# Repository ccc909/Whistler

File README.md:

# Whistler: 16-Channel USB MEMS Microphone Array (Open Hardware)

Whistler is an open-source 16-channel circular MEMS microphone array. It plugs
into a computer over USB-C and works as a standard USB Audio Class 2 (UAC2)
microphone, with no drivers to install. An XMOS XU316 (xcore.ai) captures the
16 PDM microphones and streams them at 48 kHz. This repository has the KiCad
PCB design files, a BOM and JLCPCB production files, and the firmware.

| Mic array | Motherboard (top) | Motherboard (bottom) |
|---|---|---|
|  |  |  |

<p align="center"><em>A phone playing a 3 kHz tone is carried once around the array.<br>
Top: the phone video and the direction-of-arrival plot. Bottom: the 16 raw
channels and each mic's level at 3 kHz.</em></p>

## Key features

- **16 microphones:** Infineon IM72D128 PDM MEMS mics on a 188 mm circle with
  36.7 mm spacing. The array is designed for beamforming from about 1 kHz up to
  4.7 kHz, its spatial-aliasing limit.
- **USB audio:** an XMOS XU316 (xcore.ai) streams all 16 channels as a
  48 kHz USB Audio Class 2 microphone over USB-C.
- **Standalone:** boots from on-board QSPI flash, runs on USB bus power, and
  takes firmware updates over USB (DFU).
- **Two boards:** a 2-layer mic array and a 4-layer, 28.8 × 60.2 mm
  motherboard, linked by a 24-pin FFC.
- **Ready to order:** gerbers, a BOM with LCSC numbers, and a JLCPCB
  pick-and-place file for each board.
- **Measured:** a whistle at 125 m outdoors came through at 39 dB SNR on a
  single mic and 51 dB with the 16-mic beam, a 12.7 dB array gain. See
  [docs/measurements.md](docs/measurements.md).

<p align="center"><em>Field test: a whistle blown 125 m away at dusk, with crickets and birds in
the background.<br>Left: a single mic. Right: all 16 mics beamformed toward it.</em></p>

## Microphones

The array uses 16 Infineon [IM72D128V01](https://www.infineon.com/dgdl/Infineon-IM72D128-DataSheet-v01_01-EN.pdf)
XENSIV PDM MEMS microphones, running at 1.8 V with a 3.072 MHz PDM clock (the
datasheet's high-performance mode). Key datasheet figures at that setting:

| Parameter | Value |
|---|---|
| Signal-to-noise ratio | 72 dB(A) |
| Sensitivity | −36 dBFS ±1 dB (1 kHz, 94 dB SPL) |
| Acoustic overload point | 128 dB SPL (10% THD) |
| Dynamic range | 106 dB |
| THD | 0.5% at 94 dB SPL |
| Frequency response | −3 dB at 20 Hz, +3 dB at 19 kHz |
| Directivity | Omnidirectional |
| Ingress protection | IP57 (dust and water) |
| Supply current | 980 µA per mic (typical) |
| Package | 4 × 3 × 1.2 mm LGA |

## BOM cost

The table gives the parts cost per board in USD, not counting PCBs or assembly.
Prices were taken from LCSC on 2026-10-25, with each line rounded up to LCSC's
minimum order:

| | 1 board | 10 boards | 100 boards |
|---|---|---|---|
| Mic array | $48.96 | $34.87 | $31.40 |
| Motherboard | $27.09 | $16.34 | $14.81 |
| **Both** | **$76.05** | **$51.21** | **$46.21** |

Most of the cost is the 16 microphones ($33.57 per array at 10 boards) and the
XU316 ($10.04). LCSC doesn't sell the IM72D128 directly, so the mics are priced
from JLCPCB's parts library. FB11 can be any 0402 ferrite bead of about 600 Ω at
100 MHz.

<details>
<summary>Mic array: price per part</summary>

| Part | LCSC | Qty | 1 board | 10 boards | 100 boards |
|---|---|---|---|---|---|
| IM72D128 MEMS microphone | C5119248 | 16 | $43.36 | $33.57 | $30.37 |
| 24-pin FFC connector, Hirose FH12 | C202112 | 1 | $0.52 | $0.47 | $0.42 |
| TPS7A2018 1.8 V LDO | C963430 | 1 | $1.30 | $0.26 | $0.21 |
| 74LVC125 buffer | C6057 | 1 | $0.83 | $0.17 | $0.13 |
| 1 µF capacitor, 0402 | C14445 | 19 | $0.53 | $0.10 | $0.08 |
| 10 µF capacitor, 0603 | C18800 | 1 | $0.38 | $0.08 | $0.06 |
| 4.7 µF capacitor, 0603 | C1705 | 4 | $0.64 | $0.06 | $0.05 |
| 100 nF capacitor, 0402 | C1525 | 17 | $0.36 | $0.06 | $0.05 |
| LED, 0603 | C12624 | 1 | $0.58 | $0.06 | $0.01 |
| 33 Ω resistor, 0402 | C25105 | 16 | $0.11 | $0.02 | $0.01 |
| 22 Ω resistor, 0402 | C25092 | 4 | $0.12 | $0.01 | <$0.01 |
| 470 Ω resistor, 0402 | C25117 | 1 | $0.12 | $0.01 | <$0.01 |
| Ferrite bead, 0402 | C96691 | 1 | $0.10 | $0.01 | $0.01 |
| **Total** | | | **$48.96** | **$34.87** | **$31.40** |

</details>

<details>
<summary>Motherboard: price per part</summary>

| Part | LCSC | Qty | 1 board | 10 boards | 100 boards |
|---|---|---|---|---|---|
| XU316 xcore.ai processor | C6938291 | 1 | $10.36 | $10.04 | $10.04 |
| W25Q128JW 128 Mbit QSPI flash | C2763561 | 1 | $3.40 | $2.89 | $2.28 |
| USB-C receptacle, GCT USB4105 | C3025063 | 1 | $1.47 | $1.21 | $0.91 |
| 24-pin FFC connector, Hirose FH12 | C202112 | 1 | $0.52 | $0.47 | $0.42 |
| 750 mA resettable fuse, 1206 | C371166 | 1 | $1.08 | $0.22 | $0.17 |
| 2×10 1.27 mm header, xTAG | C22438125 | 1 | $0.81 | $0.16 | $0.13 |
| 2.2 µH inductor | C337893 | 1 | $0.78 | $0.16 | $0.13 |
| 22 µF capacitor, 0603 | C109448 | 1 | $0.76 | $0.15 | $0.13 |
| AP2112K 3.3 V LDO | C23380830 | 1 | $0.56 | $0.11 | $0.09 |
| 100 nF capacitor, 0402 | C1525 | 29 | $0.36 | $0.10 | $0.08 |
| AP2112K 1.8 V LDO | C3021123 | 1 | $0.49 | $0.10 | $0.08 |
| 24 MHz crystal, 3225 | C70590 | 1 | $0.48 | $0.10 | $0.08 |
| Ferrite bead, 0603 | C85833 | 1 | $0.92 | $0.09 | $0.02 |
| 10 µF capacitor, 0603 | C96446 | 2 | $0.87 | $0.09 | $0.07 |
| TLV62569 buck converter | C141836 | 1 | $0.36 | $0.07 | $0.06 |
| TVS diode, 0402 | C558615 | 2 | $0.69 | $0.07 | $0.05 |
| 4.7 µF capacitor, 0603 | C1705 | 3 | $0.64 | $0.06 | $0.04 |
| 1 µF capacitor, 0402 | C52923 | 5 | $0.64 | $0.06 | $0.03 |
| LED, 0603 | C2289 | 1 | $0.53 | $0.05 | $0.01 |
| 18 pF capacitor, 0402 | C1549 | 2 | $0.27 | $0.03 | $0.01 |
| 5.1 kΩ resistor, 0402 | C25905 | 2 | $0.23 | $0.02 | <$0.01 |
| 49.9 kΩ resistor, 0402 | C137969 | 1 | $0.22 | $0.02 | <$0.01 |
| 100 kΩ resistor, 0402 | C25741 | 1 | $0.15 | $0.01 | <$0.01 |
| 1 MΩ resistor, 0402 | C26083 | 1 | $0.15 | $0.01 | <$0.01 |
| 680 Ω resistor, 0402 | C25130 | 1 | $0.12 | $0.01 | <$0.01 |
| 470 Ω resistor, 0402 | C25117 | 1 | $0.12 | $0.01 | <$0.01 |
| 10 kΩ resistor, 0402 | C25744 | 3 | $0.11 | $0.01 | <$0.01 |
| **Total** | | | **$27.09** | **$16.34** | **$14.81** |

</details>

## Project structure

| Folder | Contents |
|---|---|
| [`mic-array/`](mic-array), [`motherboard/`](motherboard) | KiCad 10 projects; ordering files are in each `production/` folder |
| [`lib/`](lib) | Symbols, footprints and 3D models for both boards |
| [`firmware/`](firmware) | XU316 firmware: a prebuilt image and its source |
| [`docs/`](docs) | Renders, [manufacturing notes](docs/manufacturing.md) and [measurements](docs/measurements.md) |

## Quick start

- **Edit:** open either `*.kicad_pro` in KiCad 10. All libraries are included.
- **Order:** upload a board's `production/` files to JLCPCB. Read
  [docs/manufacturing.md](docs/manufacturing.md) first.
- **Flash:** program a new motherboard once over an xTAG on J2. After that,
  updates go over USB (DFU); see [firmware/README.md](firmware/README.md).

```bash
xflash --factory firmware/bin/whistler-mic-aggregator.xe
```

## Licence

Copyright 2026 the Whistler authors.

- **Hardware:** [CERN-OHL-S v2](LICENSE).
- **Firmware:** XMOS Public Licence v1 ([`firmware/LICENSE-XMOS.rst`](firmware/LICENSE-XMOS.rst)).
- **Library parts:** keep their own licences ([`lib/README.md`](lib/README.md)).

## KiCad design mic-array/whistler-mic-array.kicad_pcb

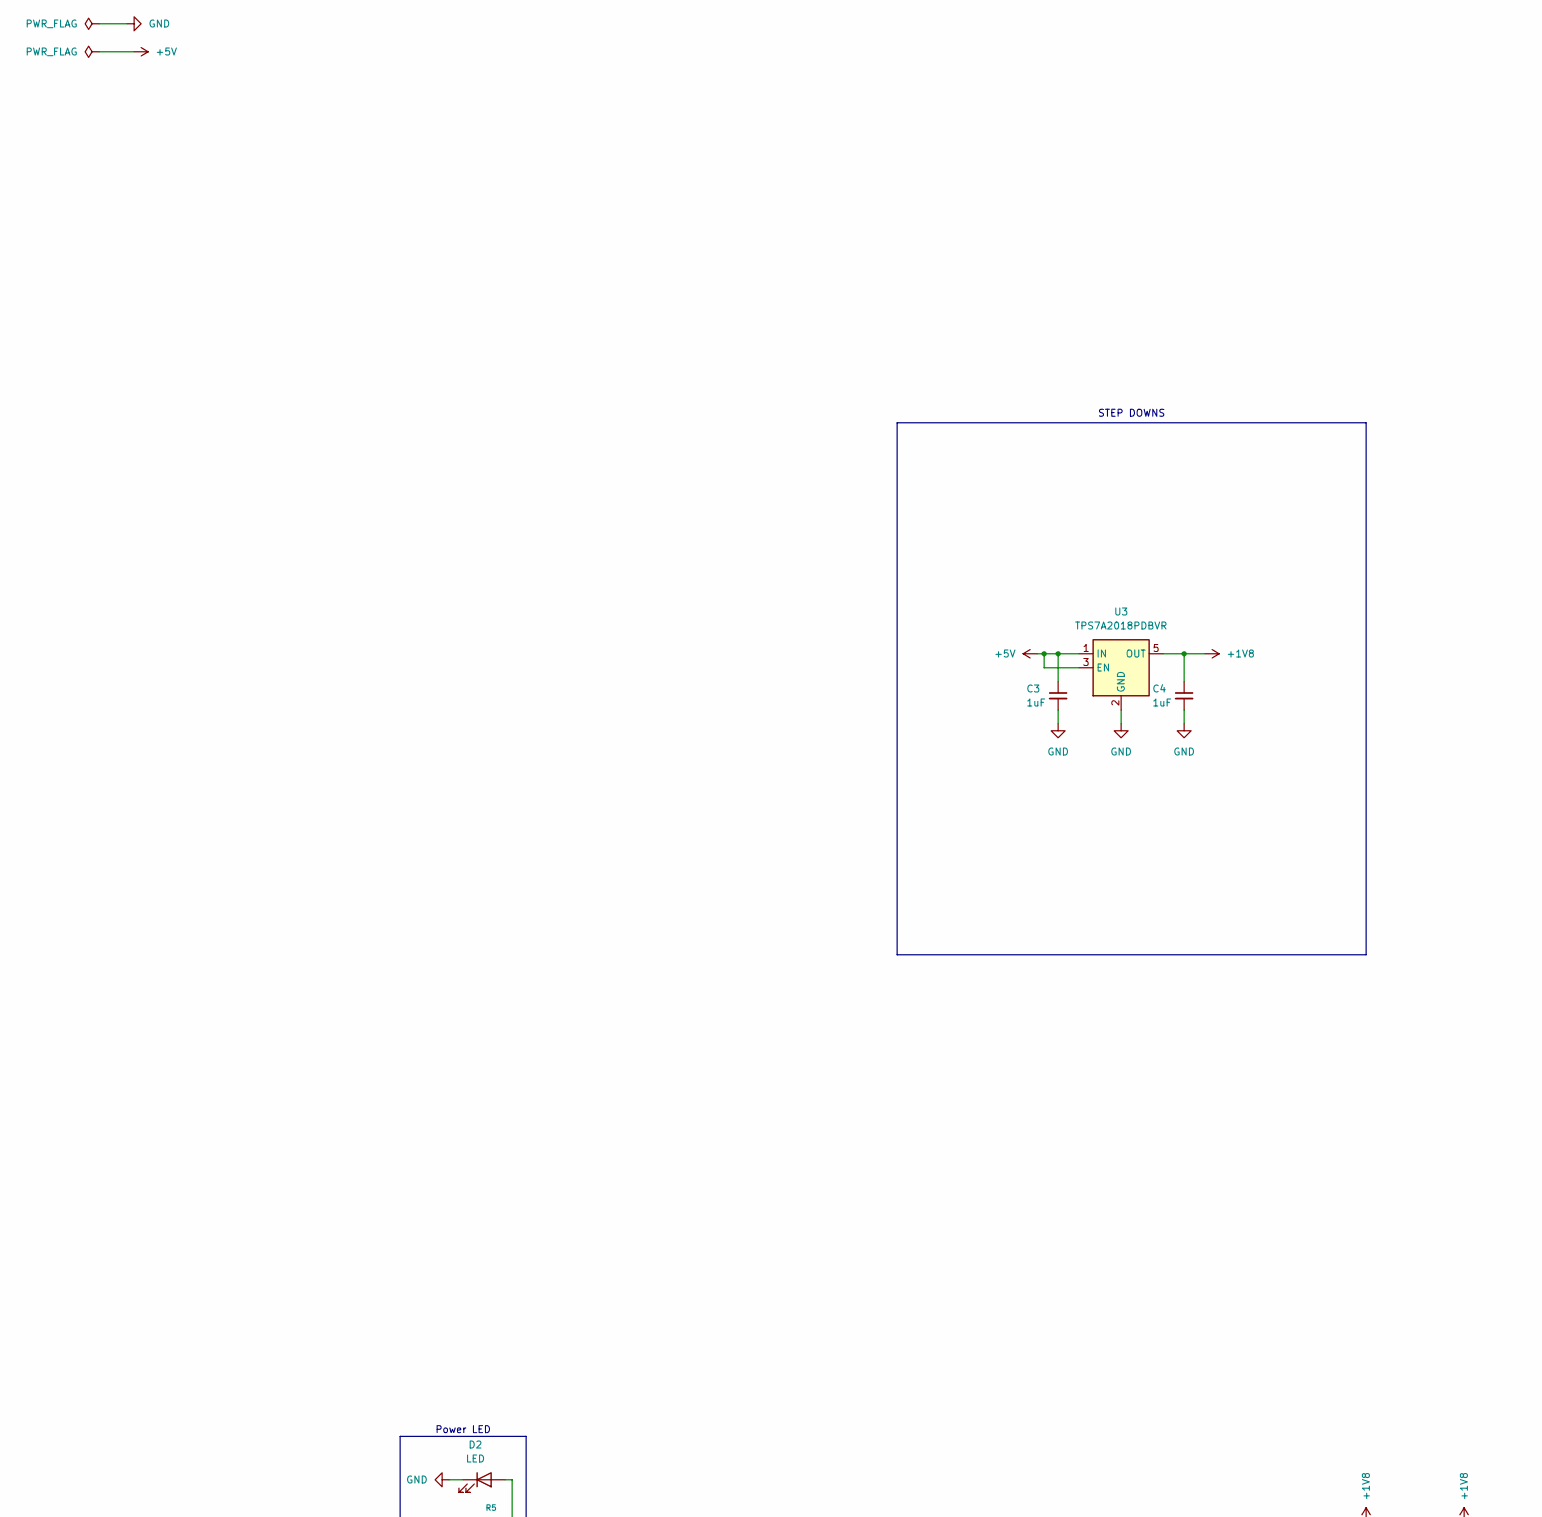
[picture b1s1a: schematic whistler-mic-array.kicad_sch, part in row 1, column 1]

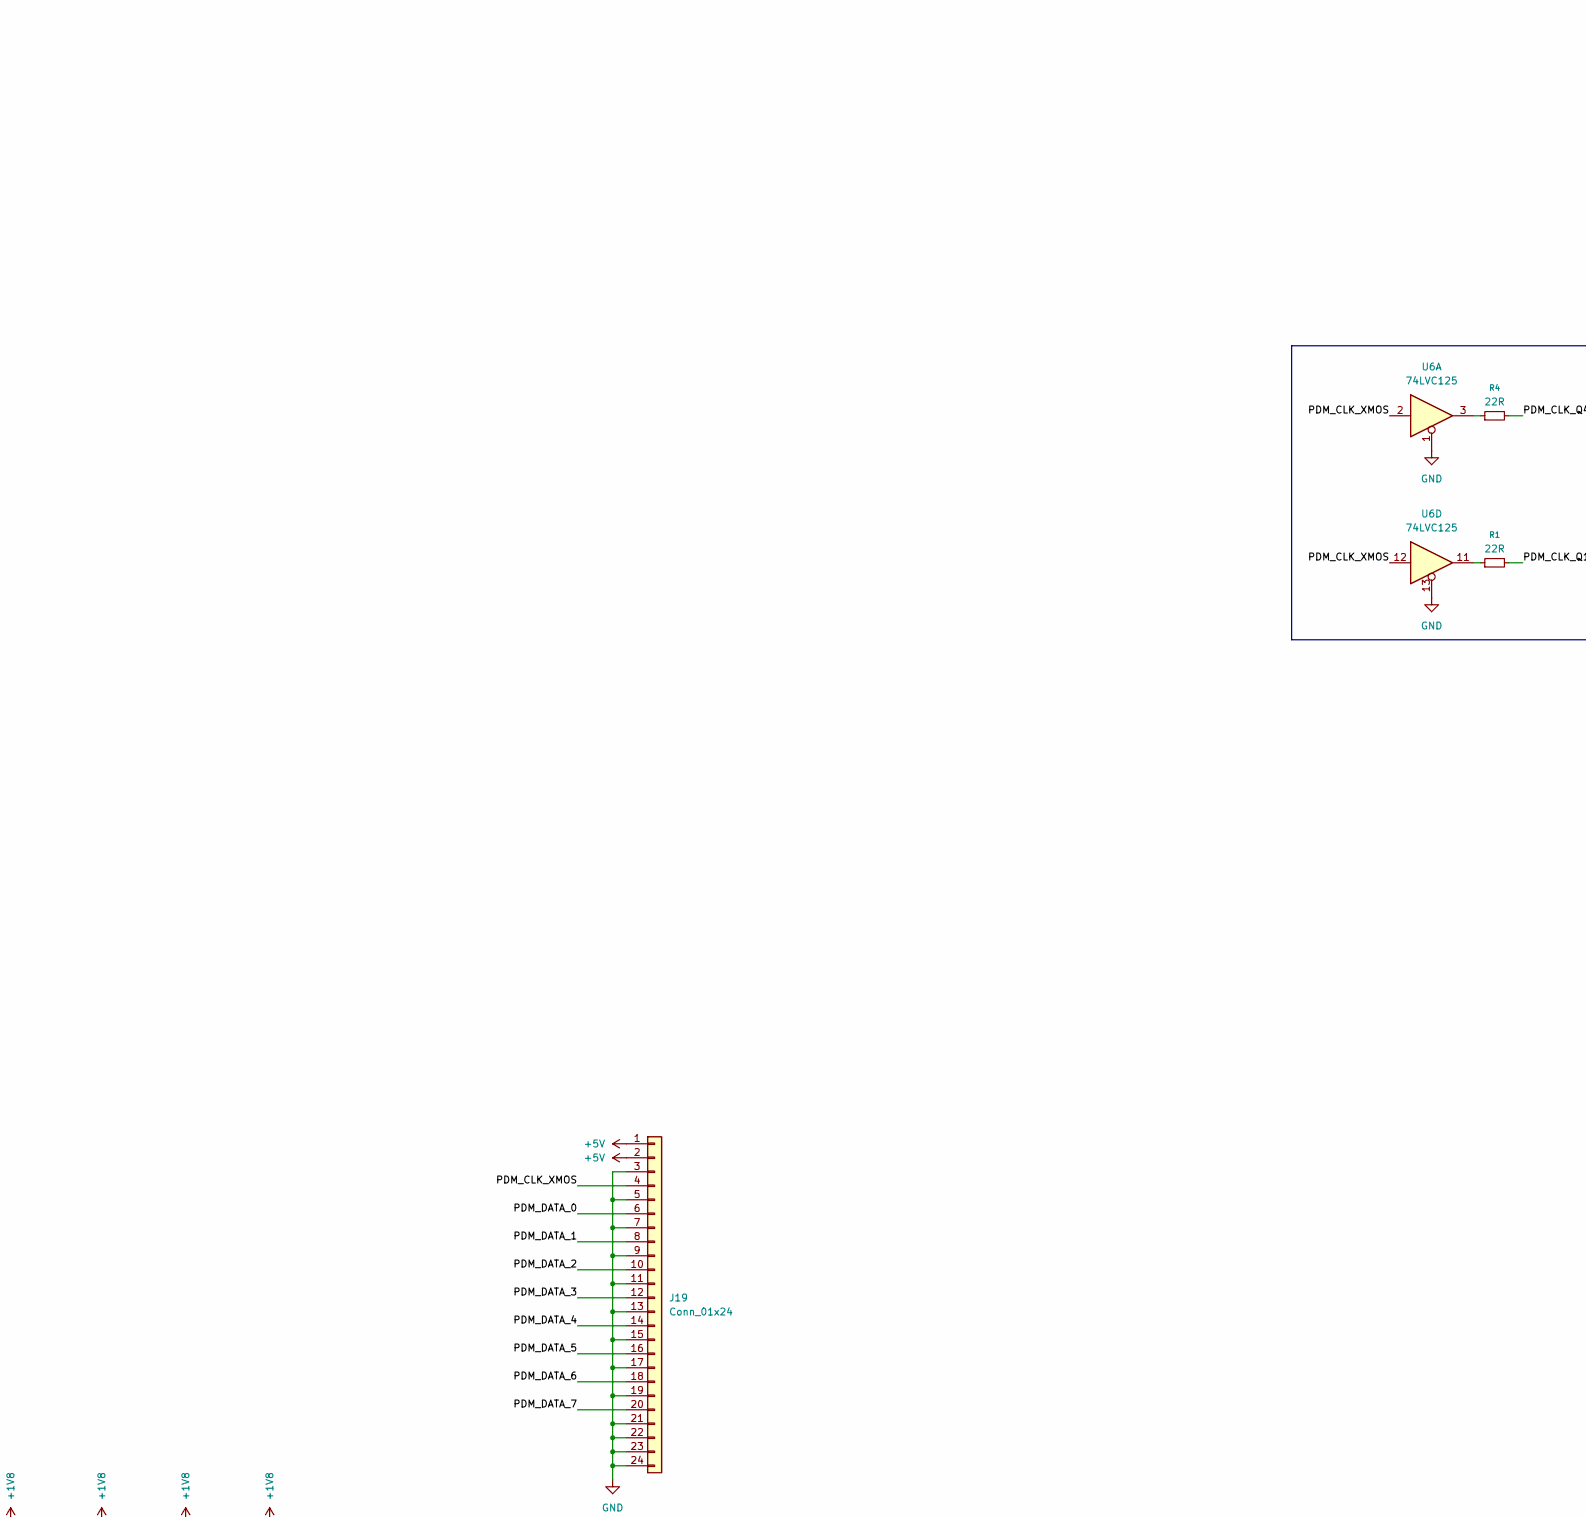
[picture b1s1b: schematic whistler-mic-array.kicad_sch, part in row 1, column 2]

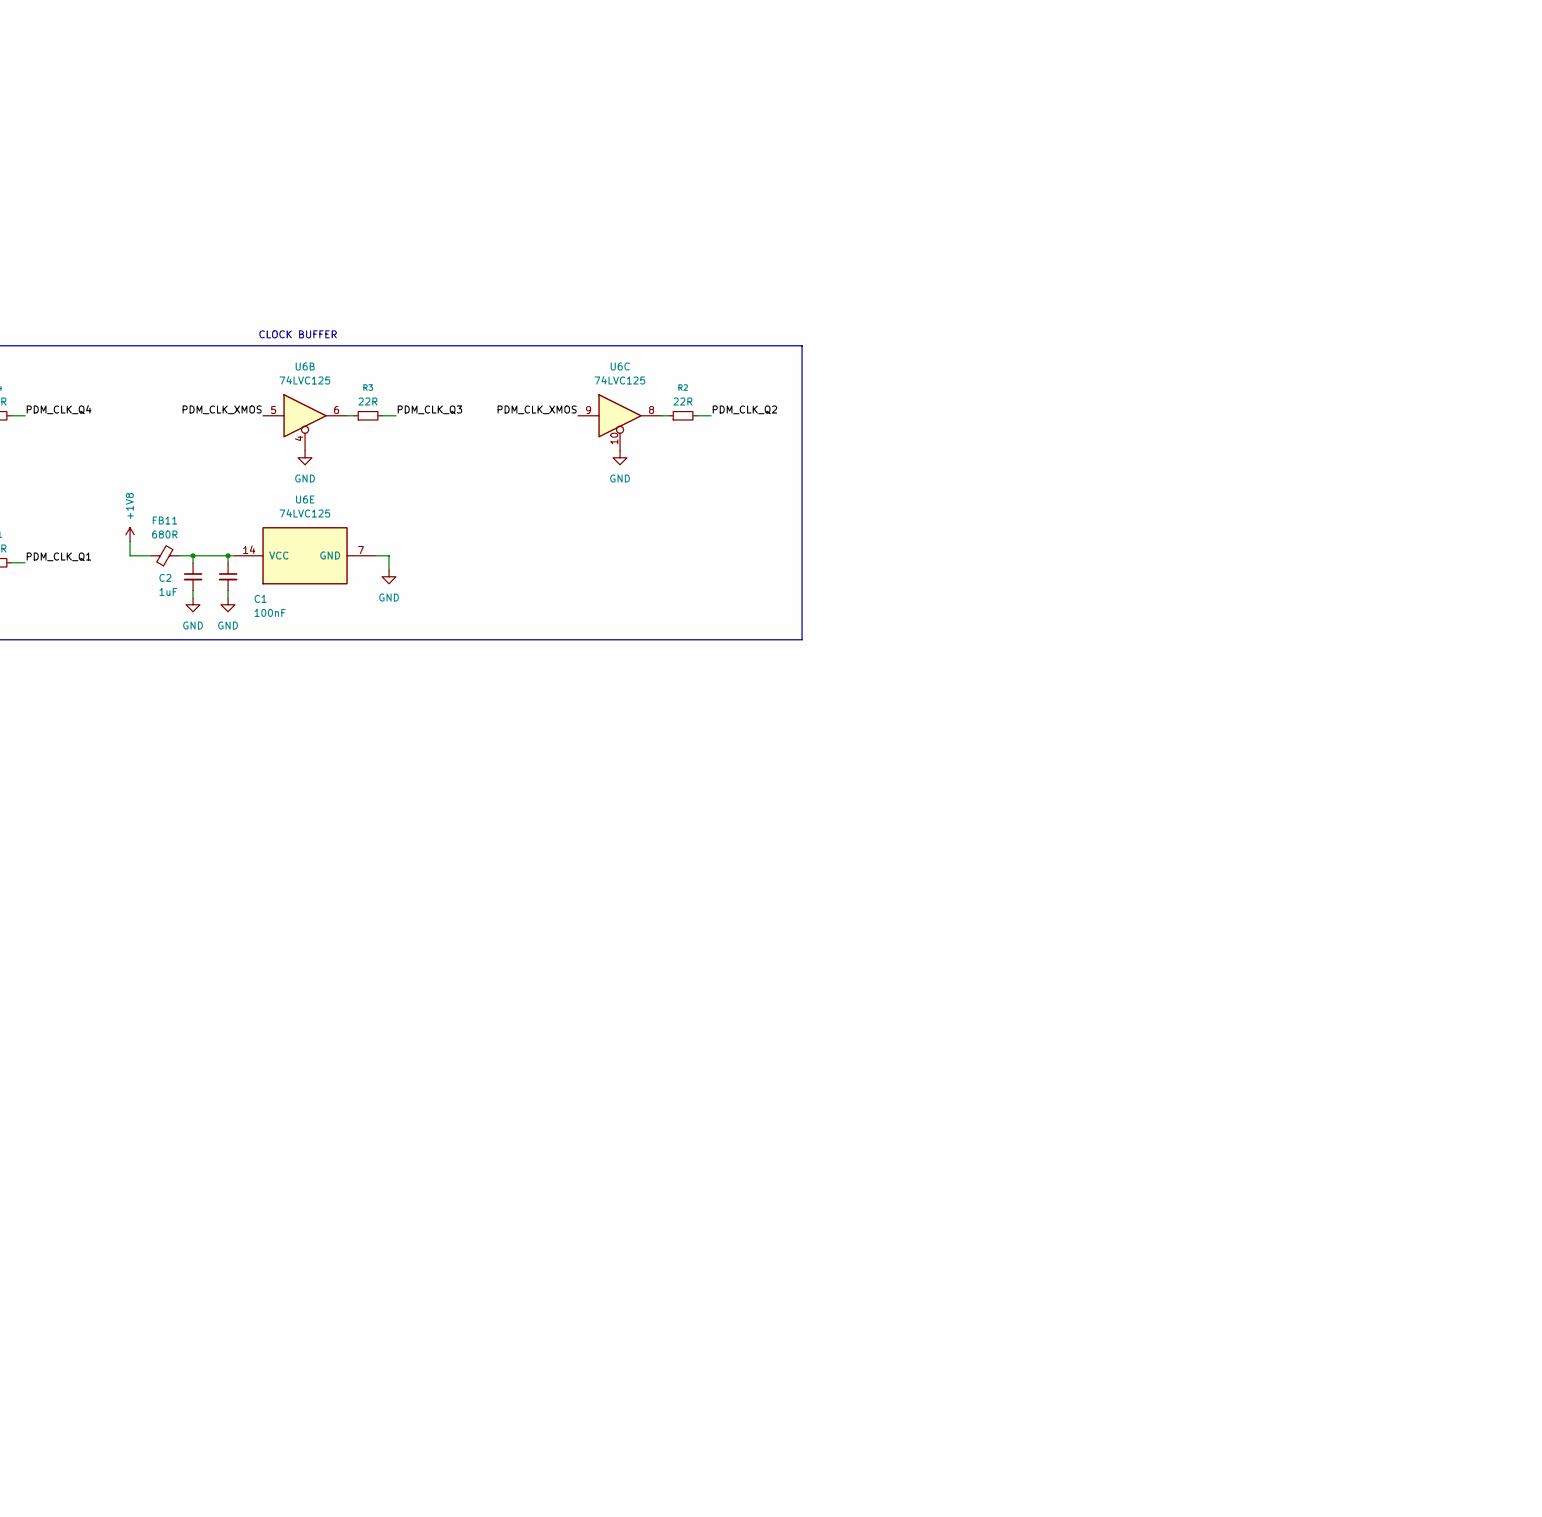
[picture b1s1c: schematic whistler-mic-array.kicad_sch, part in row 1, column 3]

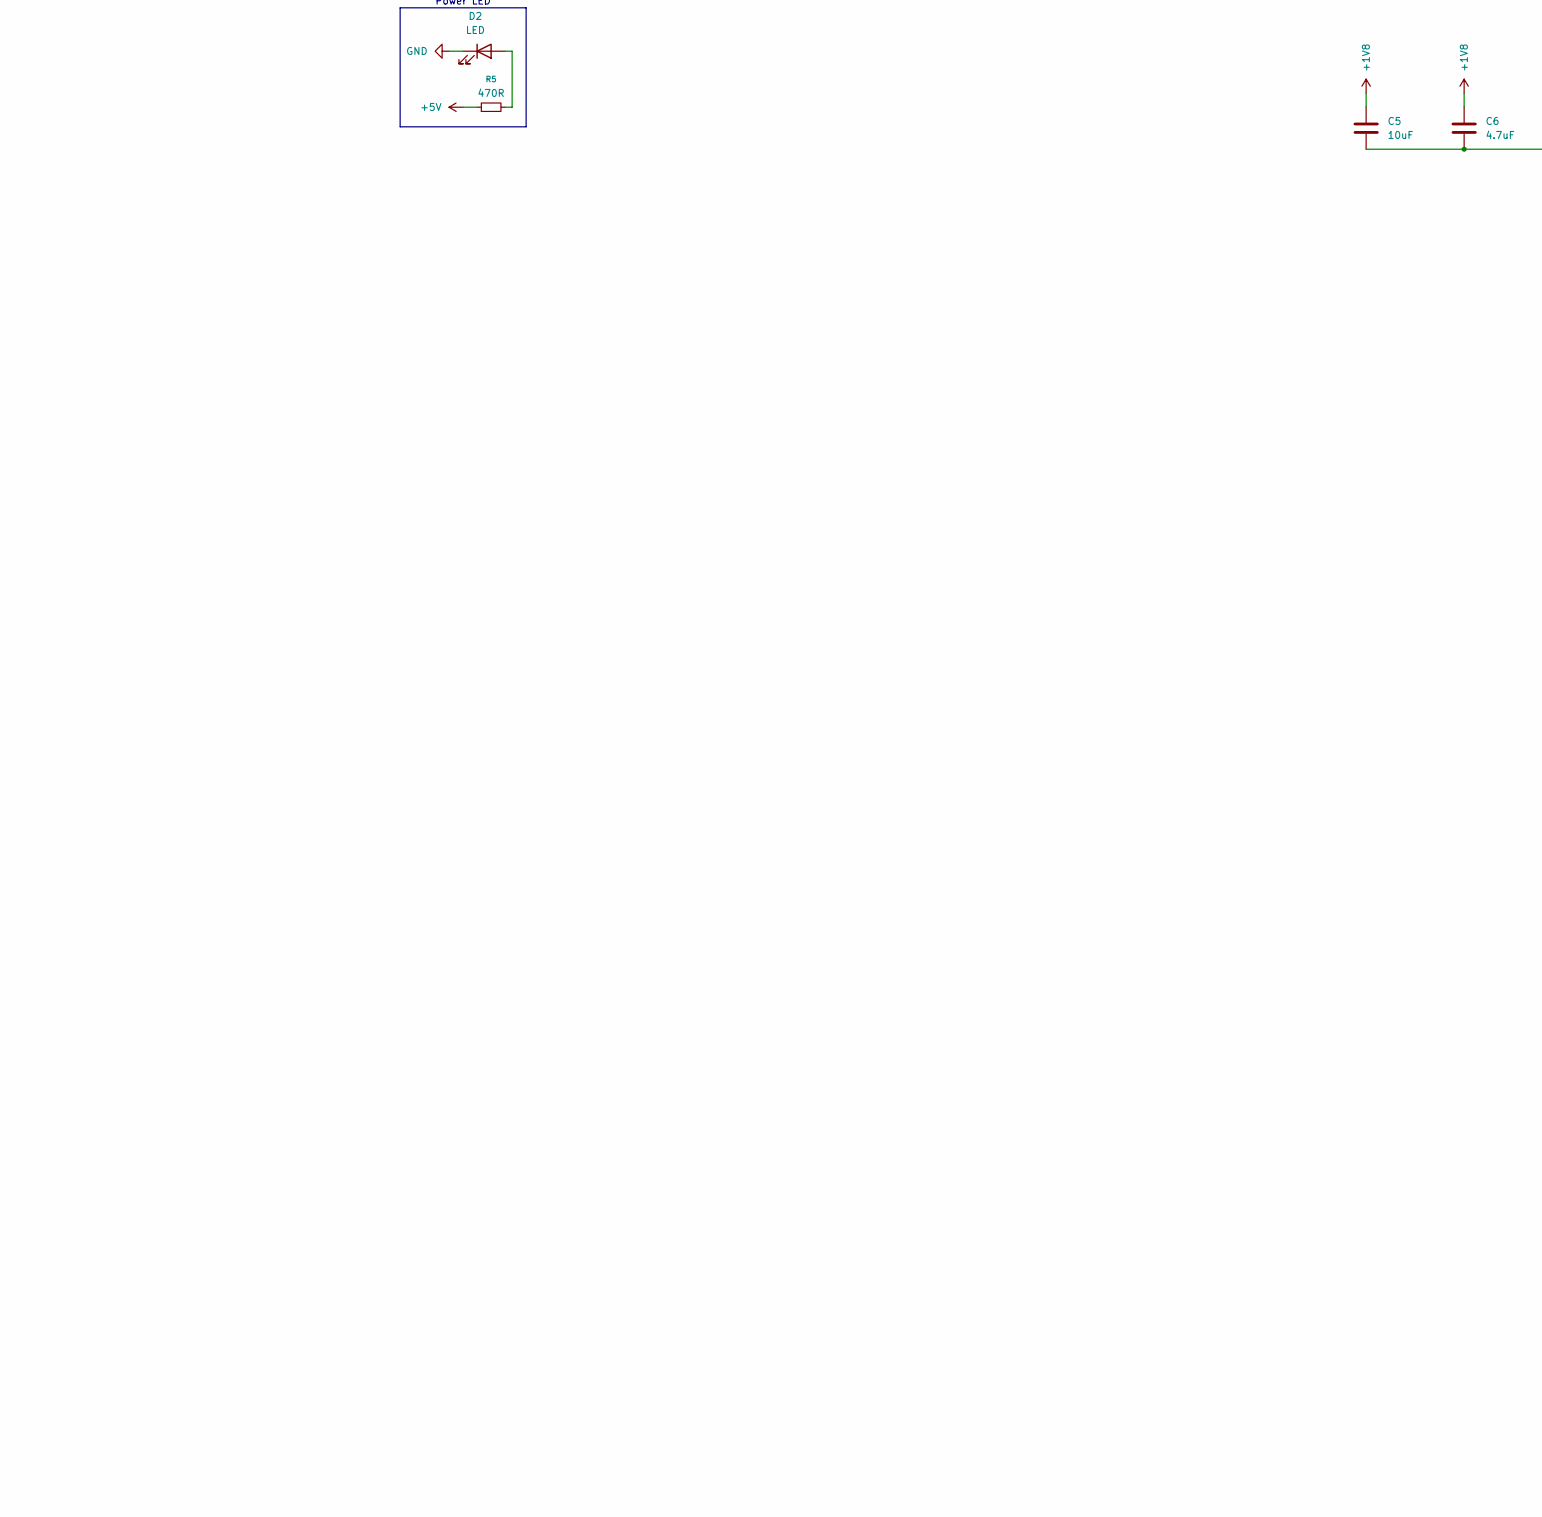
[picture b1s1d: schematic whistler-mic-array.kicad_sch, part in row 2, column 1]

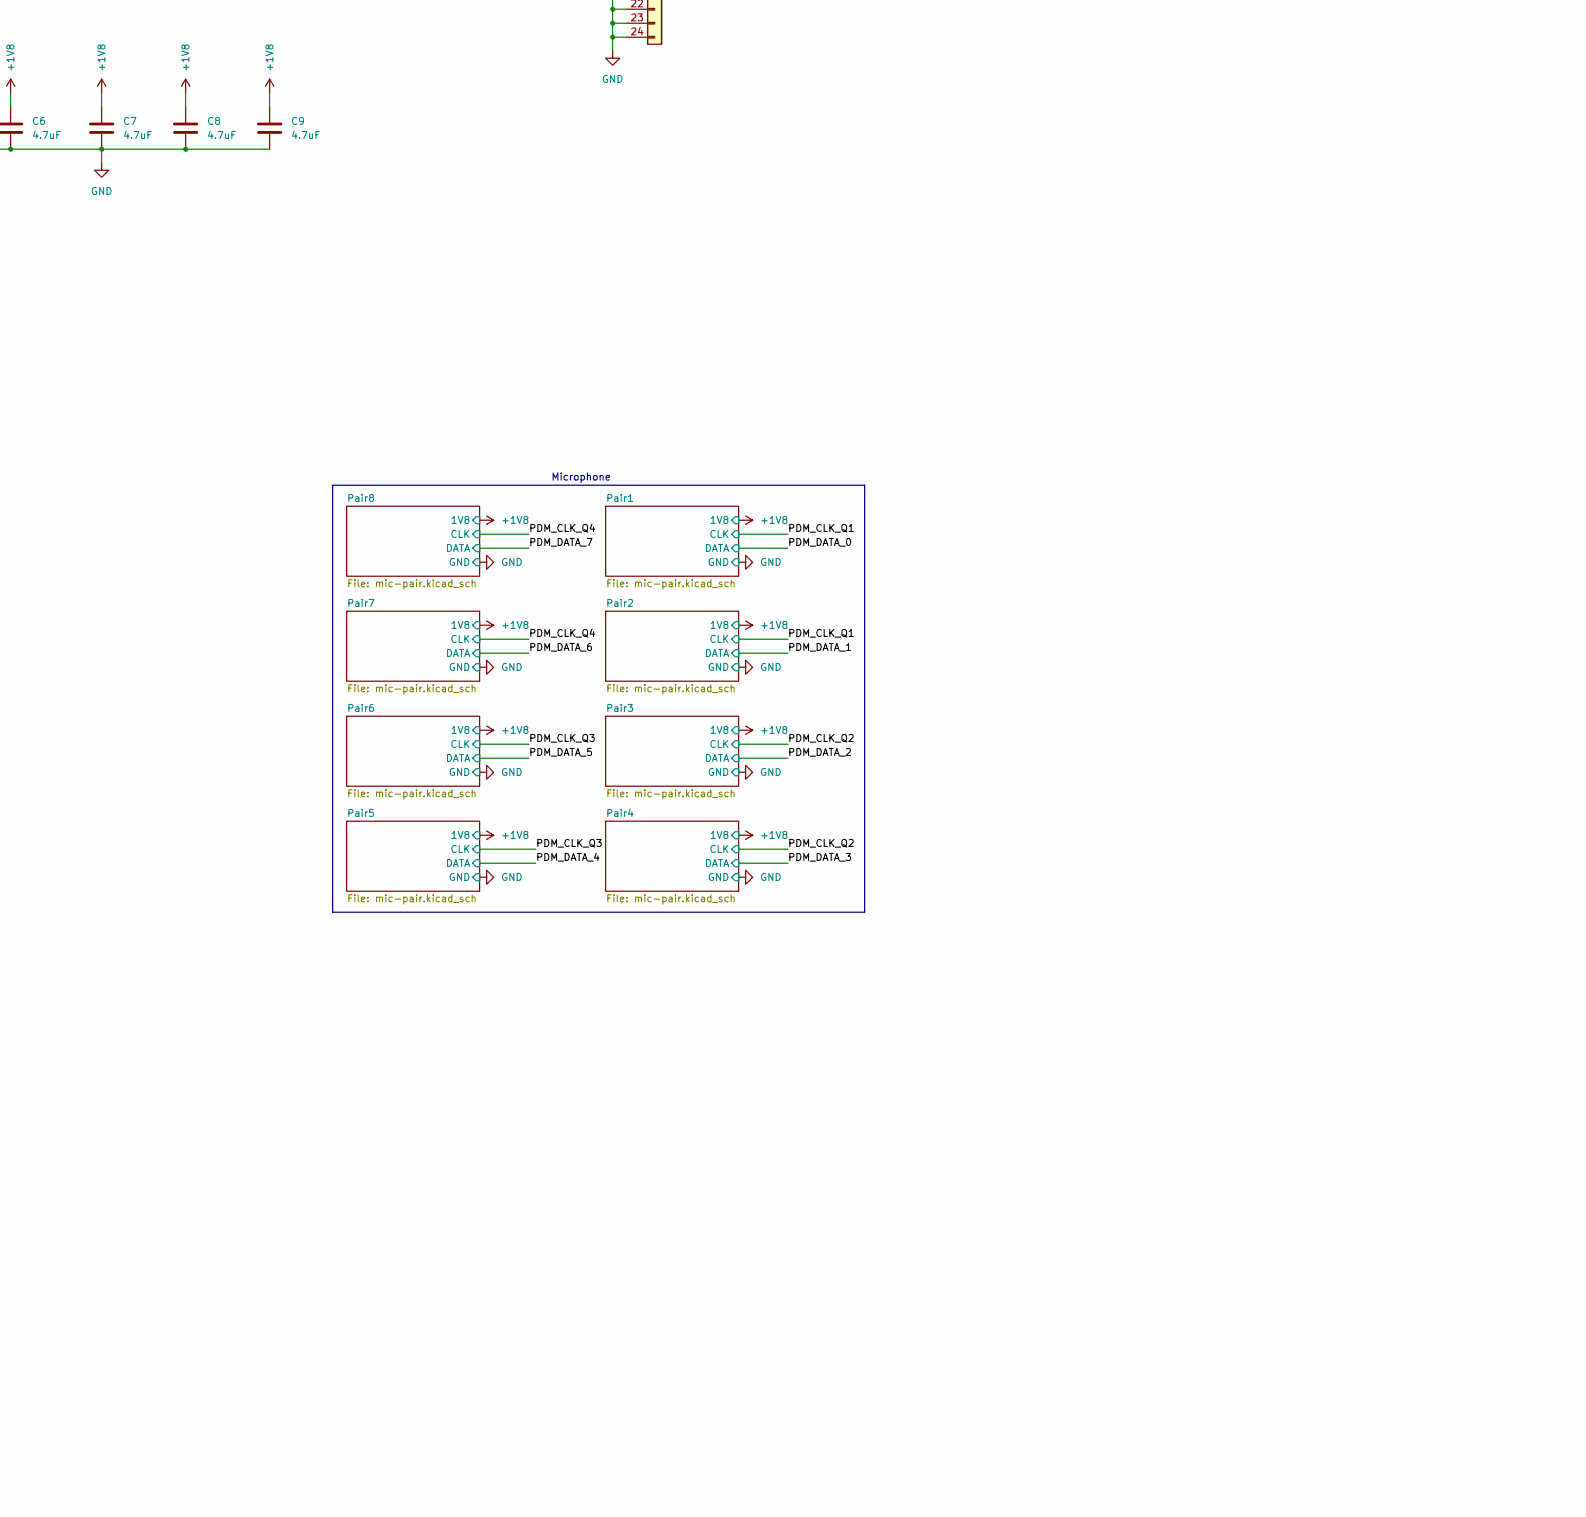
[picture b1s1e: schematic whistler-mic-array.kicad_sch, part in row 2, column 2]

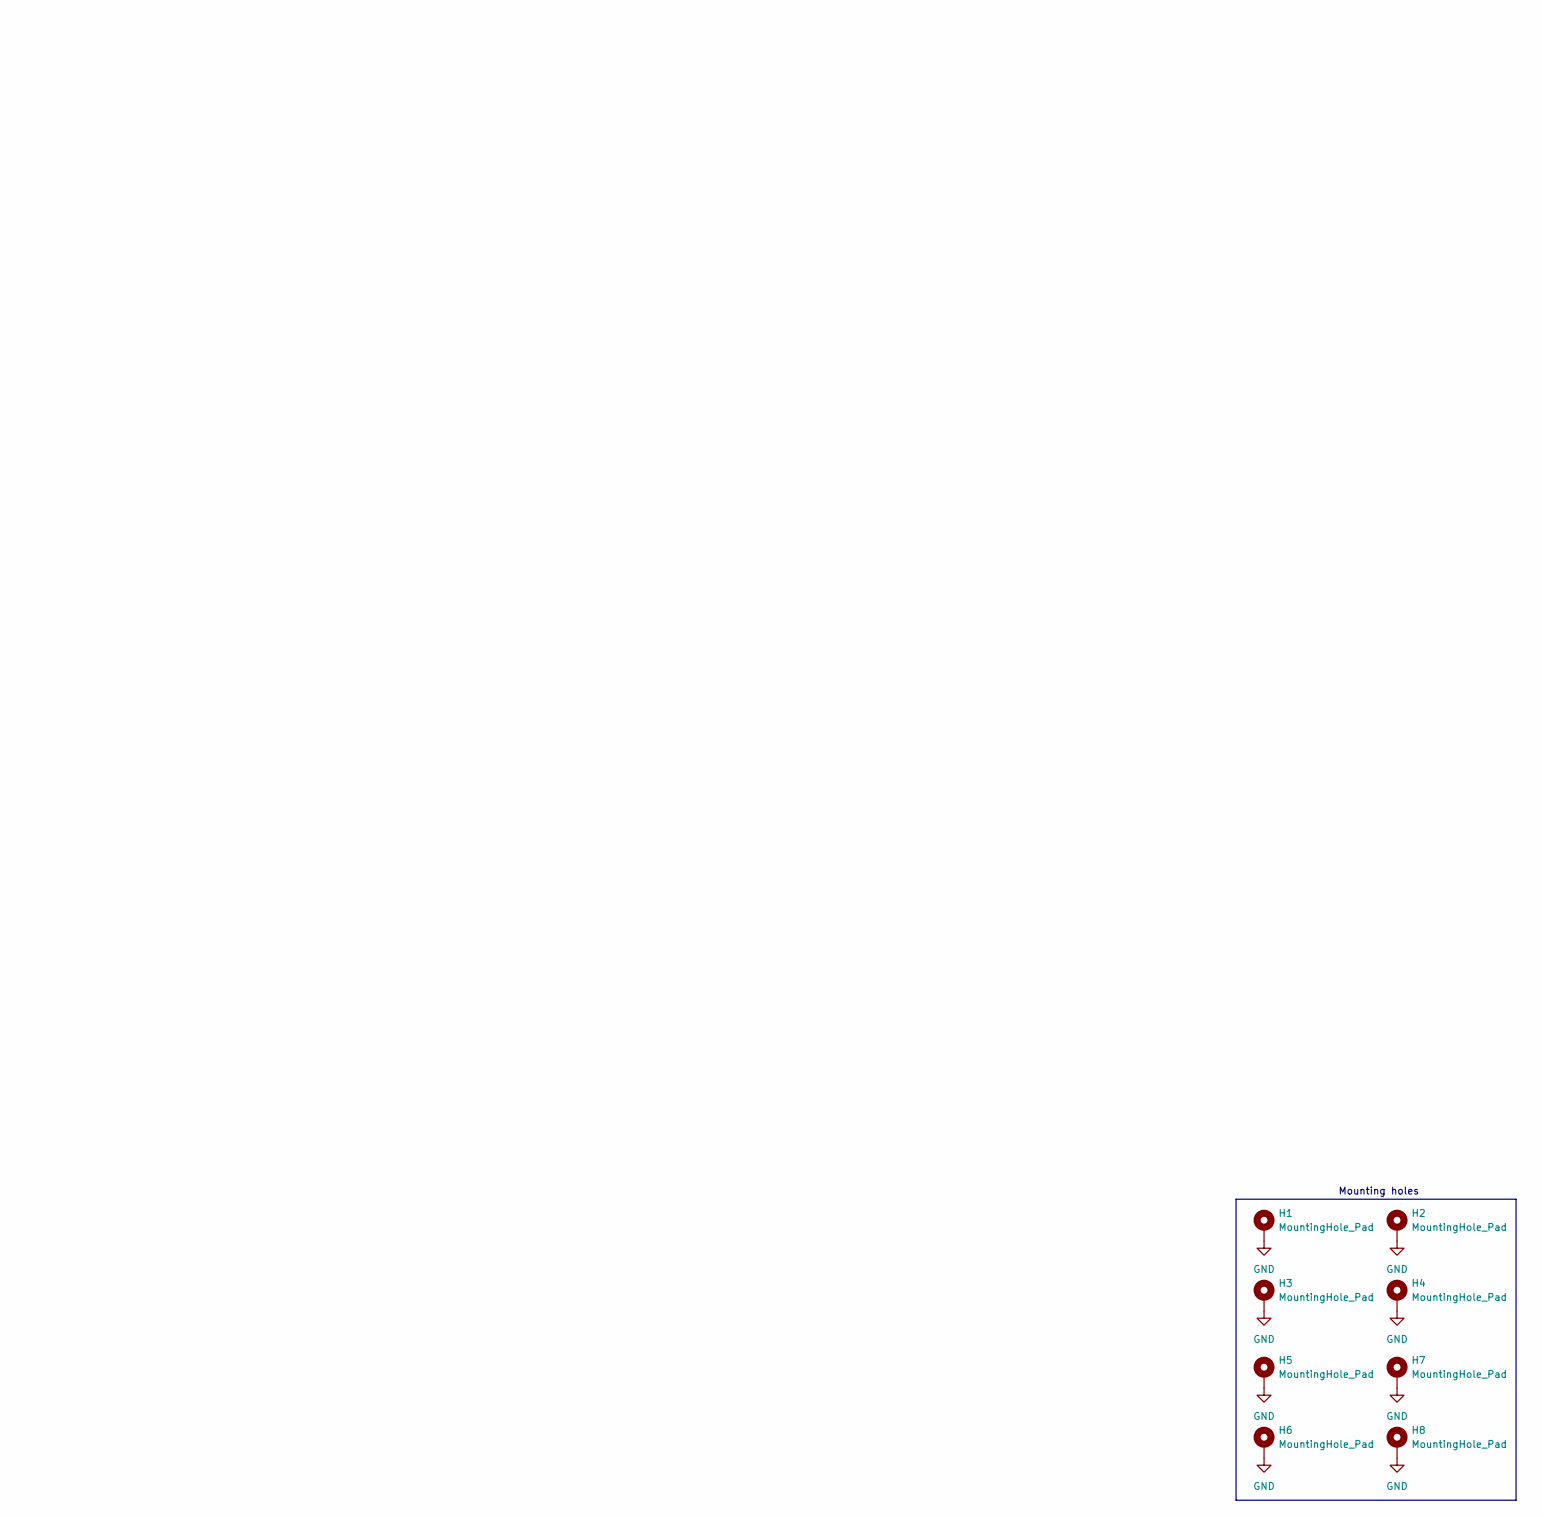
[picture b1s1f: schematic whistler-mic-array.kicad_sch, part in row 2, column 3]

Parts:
C1: 100nF; C_0402_1005Metric; LCSC C1525
C2, C3, C4: 1uF; C_0402_1005Metric; LCSC C14445
C5: 10uF; C_0603_1608Metric; LCSC C18800
C6, C7, C8, C9: 4.7uF; C_0603_1608Metric; LCSC C1705
D2: LED; LED_0603_1608Metric; LCSC C12624
FB11: 680R; C_0402_1005Metric; LCSC C96691
H1, H2, H3, H4, H5, H6, H7, H8: MountingHole_Pad; MountingHole_3.2mm_M3_Pad
J19: Conn_01x24; Hirose_FH12-24S-0.5SH_1x24-1MP_P0.50mm_Horizontal; LCSC C202112
R1, R2, R3, R4: 22R; R_0402_1005Metric; LCSC C25092
R5: 470R; R_0402_1005Metric; LCSC C25117
U3: TPS7A2018PDBVR; SOT-23-5; LCSC C963430
U6: 74LVC125; SOIC-14_3.9x8.7mm_P1.27mm; LCSC C6057

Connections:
+1V8: C4.1, C5.1, C6.1, C7.1, C8.1, C9.1, FB11.1, U3.5 (OUT); also elsewhere on the board
+5V: C3.1, J19.1, J19.2, R5.1, U3.1 (IN), U3.3 (EN)
/PDM_CLK_Q1: R1.2; also elsewhere on the board
/PDM_CLK_Q2: R2.2; also elsewhere on the board
/PDM_CLK_Q3: R3.2; also elsewhere on the board
/PDM_CLK_Q4: R4.2; also elsewhere on the board
/PDM_CLK_XMOS: J19.4, U6.2, U6.5, U6.9, U6.12
/PDM_DATA_0: J19.6; also elsewhere on the board
/PDM_DATA_1: J19.8; also elsewhere on the board
/PDM_DATA_2: J19.10; also elsewhere on the board
/PDM_DATA_3: J19.12; also elsewhere on the board
/PDM_DATA_4: J19.14; also elsewhere on the board
/PDM_DATA_5: J19.16; also elsewhere on the board
/PDM_DATA_6: J19.18; also elsewhere on the board
/PDM_DATA_7: J19.20; also elsewhere on the board
GND: C1.2, C2.2, C3.2, C4.2, C5.2, C6.2, C7.2, C8.2, C9.2, D2.1 (K), H1.1 (1_1), H2.1, H3.1 (1_1), H4.1 (1_1), H5.1, H6.1 (1_1), H7.1 (1_1), H8.1 (1_1), J19.3, J19.5, J19.7, J19.9, J19.11, J19.13, J19.15, J19.17, J19.19, J19.21, J19.22, J19.23, J19.24, J19.MP, U3.2 (GND), U6.1, U6.4, U6.7 (GND), U6.10, U6.13; also elsewhere on the board
unnamed: D2.2 (A), R5.2
unnamed: R1.1, U6.11
unnamed: R2.1, U6.8
unnamed: R3.1, U6.6
unnamed: R4.1, U6.3
unnamed: C1.1, C2.1, FB11.2, U6.14 (VCC)

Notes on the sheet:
Microphone
STEP DOWNS
Mounting holes
Power LED
CLOCK BUFFER

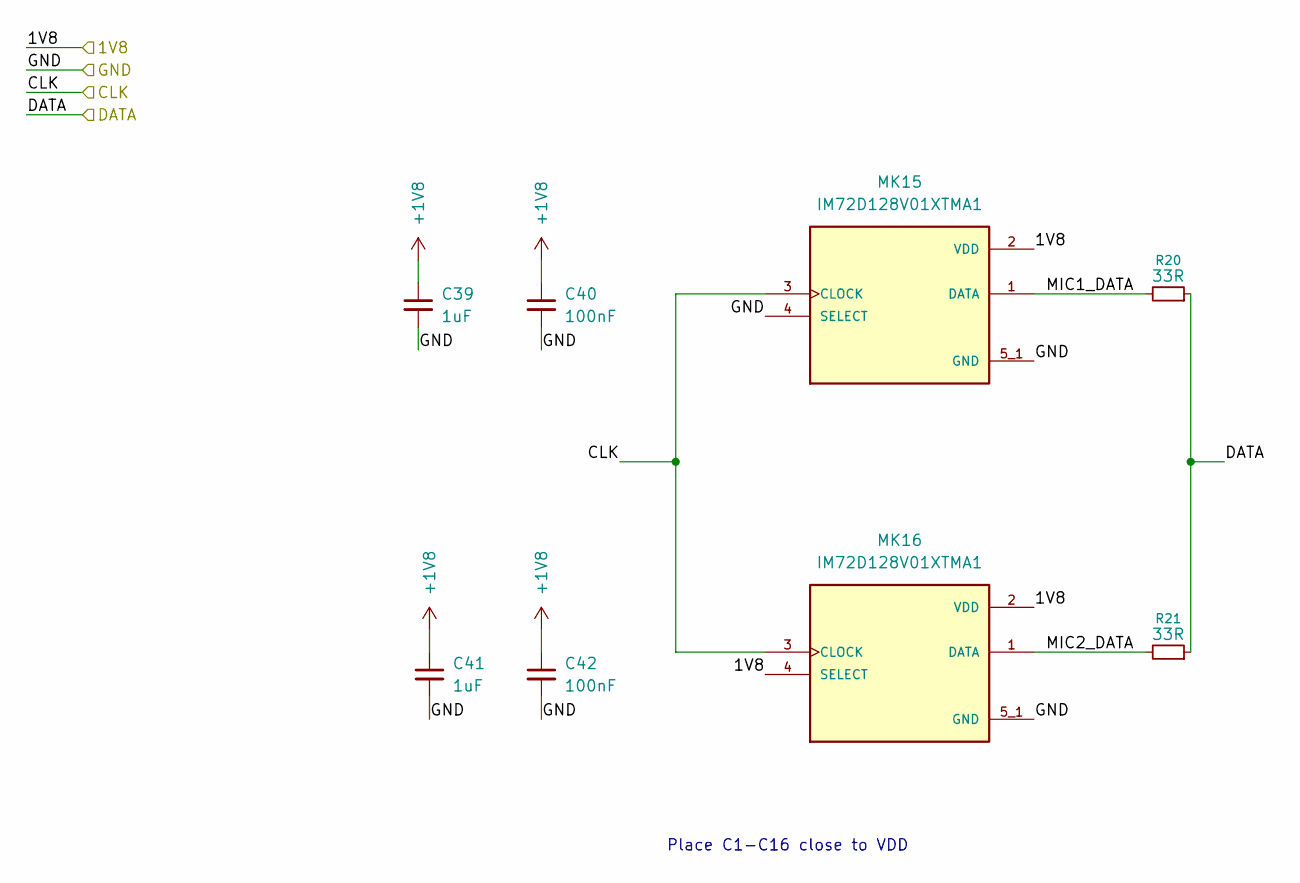
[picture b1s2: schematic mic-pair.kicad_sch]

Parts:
C39, C41: 1uF; C_0402_1005Metric; LCSC C14445
C40, C42: 100nF; C_0402_1005Metric; LCSC C1525
MK15, MK16: IM72D128V01XTMA1; MIC_IM72D128V01XTMA1; PARTREV 2022-05-05; LCSC C5119248
R20, R21: 33R; R_0402_1005Metric; LCSC C25105

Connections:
+1V8: C39.1, C40.1, C41.1, C42.1, MK15.2 (VDD), MK16.2 (VDD), MK16.4 (SELECT); also elsewhere on the board
/PDM_CLK_Q4: MK15.3 (CLOCK), MK16.3 (CLOCK); also elsewhere on the board
/PDM_DATA_7: R20.1, R21.1; also elsewhere on the board
/Pair8/MIC1_DATA: MK15.1 (DATA), R20.2
/Pair8/MIC2_DATA: MK16.1 (DATA), R21.2
GND: C39.2, C40.2, C41.2, C42.2, MK15.4 (SELECT), MK15.5_1 (GND), MK15.5_2 (GND), MK16.5_1 (GND), MK16.5_2 (GND); also elsewhere on the board

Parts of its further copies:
C11, C13, C15, C17, C19, C21, C23, C25, C27, C29, C31, C33, C35, C37: 1uF; C_0402_1005Metric; LCSC C14445
C12, C14, C16, C18, C20, C22, C24, C26, C28, C30, C32, C34, C36, C38: 100nF; C_0402_1005Metric; LCSC C1525
MK1, MK2, MK3, MK4, MK5, MK6, MK7, MK8, MK9, MK10, MK11, MK12, MK13, MK14: IM72D128V01XTMA1; MIC_IM72D128V01XTMA1; PARTREV 2022-05-05; LCSC C5119248
R6, R7, R8, R9, R10, R11, R12, R13, R14, R15, R16, R17, R18, R19: 33R; R_0402_1005Metric; LCSC C25105

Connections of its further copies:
+1V8: C11.1, C12.1, C13.1, C14.1, C15.1, C16.1, C17.1, C18.1, C19.1, C20.1, C21.1, C22.1, C23.1, C24.1, C25.1, C26.1, C27.1, C28.1, C29.1, C30.1, C31.1, C32.1, C33.1, C34.1, C35.1, C36.1, C37.1, C38.1, MK1.2 (VDD), MK2.2 (VDD), MK2.4 (SELECT), MK3.2 (VDD), MK4.2 (VDD), MK4.4 (SELECT), MK5.2 (VDD), MK6.2 (VDD), MK6.4 (SELECT), MK7.2 (VDD), MK8.2 (VDD), MK8.4 (SELECT), MK9.2 (VDD), MK10.2 (VDD), MK10.4 (SELECT), MK11.2 (VDD), MK12.2 (VDD), MK12.4 (SELECT), MK13.2 (VDD), MK14.2 (VDD), MK14.4 (SELECT); also elsewhere on the board
/PDM_CLK_Q1: MK1.3 (CLOCK), MK2.3 (CLOCK), MK3.3 (CLOCK), MK4.3 (CLOCK); also elsewhere on the board
/PDM_CLK_Q2: MK5.3 (CLOCK), MK6.3 (CLOCK), MK7.3 (CLOCK), MK8.3 (CLOCK); also elsewhere on the board
/PDM_CLK_Q3: MK9.3 (CLOCK), MK10.3 (CLOCK), MK11.3 (CLOCK), MK12.3 (CLOCK); also elsewhere on the board
/PDM_CLK_Q4: MK13.3 (CLOCK), MK14.3 (CLOCK); also elsewhere on the board
/PDM_DATA_0: R6.1, R7.1; also elsewhere on the board
/PDM_DATA_1: R8.1, R9.1; also elsewhere on the board
/PDM_DATA_2: R10.1, R11.1; also elsewhere on the board
/PDM_DATA_3: R12.1, R13.1; also elsewhere on the board
/PDM_DATA_4: R14.1, R15.1; also elsewhere on the board
/PDM_DATA_5: R16.1, R17.1; also elsewhere on the board
/PDM_DATA_6: R18.1, R19.1; also elsewhere on the board
/Pair1/MIC1_DATA: MK1.1 (DATA), R6.2
/Pair1/MIC2_DATA: MK2.1 (DATA), R7.2
/Pair2/MIC1_DATA: MK3.1 (DATA), R8.2
/Pair2/MIC2_DATA: MK4.1 (DATA), R9.2
/Pair3/MIC1_DATA: MK5.1 (DATA), R10.2
/Pair3/MIC2_DATA: MK6.1 (DATA), R11.2
/Pair4/MIC1_DATA: MK7.1 (DATA), R12.2
/Pair4/MIC2_DATA: MK8.1 (DATA), R13.2
/Pair5/MIC1_DATA: MK9.1 (DATA), R14.2
/Pair5/MIC2_DATA: MK10.1 (DATA), R15.2
/Pair6/MIC1_DATA: MK11.1 (DATA), R16.2
/Pair6/MIC2_DATA: MK12.1 (DATA), R17.2
/Pair7/MIC1_DATA: MK13.1 (DATA), R18.2
/Pair7/MIC2_DATA: MK14.1 (DATA), R19.2
GND: C11.2, C12.2, C13.2, C14.2, C15.2, C16.2, C17.2, C18.2, C19.2, C20.2, C21.2, C22.2, C23.2, C24.2, C25.2, C26.2, C27.2, C28.2, C29.2, C30.2, C31.2, C32.2, C33.2, C34.2, C35.2, C36.2, C37.2, C38.2, MK1.4 (SELECT), MK1.5_1 (GND), MK1.5_2 (GND), MK2.5_1 (GND), MK2.5_2 (GND), MK3.4 (SELECT), MK3.5_1 (GND), MK3.5_2 (GND), MK4.5_1 (GND), MK4.5_2 (GND), MK5.4 (SELECT), MK5.5_1 (GND), MK5.5_2 (GND), MK6.5_1 (GND), MK6.5_2 (GND), MK7.4 (SELECT), MK7.5_1 (GND), MK7.5_2 (GND), MK8.5_1 (GND), MK8.5_2 (GND), MK9.4 (SELECT), MK9.5_1 (GND), MK9.5_2 (GND), MK10.5_1 (GND), MK10.5_2 (GND), MK11.4 (SELECT), MK11.5_1 (GND), MK11.5_2 (GND), MK12.5_1 (GND), MK12.5_2 (GND), MK13.4 (SELECT), MK13.5_1 (GND), MK13.5_2 (GND), MK14.5_1 (GND), MK14.5_2 (GND); also elsewhere on the board

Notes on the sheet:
Place C1-C16 close to VDD
